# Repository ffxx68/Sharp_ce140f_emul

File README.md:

# Sharp_ce140f_emul
A hardware module emulating the Sharp CE-140F disk drive, using an SD-Card and an STM32 Nucleo microcontroller

At the time (I'm talking about mid '80s early '90s), what I thought my Sharp-PC was missing the most was a convenient way to store and load programs. Entering a BASIC listing by hand has always been one of the most frustrating tasks, in the early days of home computing. Magnetic cassettes using a standard record player used to be the most common (and affordable!) storage medium, back then. Indeed, today a software-emulated cassette interface has been developed too - [PocketTools](http://pocket.free.fr/html/soft/pocket-tools_e.html), but using disks is something definitely different!

The Sharp CE-140F Disk Driver was a rare and expensive extension for the Sharp Pocket PCs, compatible with several models:

PC-1280, PC-1280(Jap), PC-1285, PC-1403, PC-1403H, PC-1425, PC-1425(Jap), PC-1460, PC-1460(Jap), PC-1470U, PC-1475, PC-1475(Jap), EL-5500III, PC-E500, PC-E500(Jap), PC-E500S, PC-E550, PC-E650, PC-U6000. As well as the PC-1360, PC-1360K, PC-1365 and PC-1365K after 1986 (see also: [pocket.free.fr](http://pocket.free.fr/html/sharp/ce-140f_e.html?fbclid=IwAR3U31Bk95W-eKc_V7EStOoxpfgk6qsZ3UOhHXM6cb7czv4wsmH_SPU4H-8)).

The interface presented here is an emulated hardware alternative to the real CE-140F, to get a fully functional disk file management on Sharp PCs, using an SD-card as a storage medium, so that one can manage files from a Sharp PC using a modern PC.

## The PCB board

After optimizing the project with this early prototype, based upon a Nucleo L053R8 controller board (that was one I had at hand, at the time):

an Indiegogo campaign ([Sharp_ce140f_emul on Indiegogo](https://www.indiegogo.com/projects/sharp-ce-140f-disk-drive-emulator/x/32084495#/)) has succesfully crowd-funded the manufacturing of the PCB board version. This PCB holds the Nucleo (here a more powerful L432KC), the SD card, and the interface circuitry:

Here's a demonstration video, using the LOAD and SAVE commands for example, performed with the PCB version of the emulator:
 
[LOAD or SAVE demo](https://www.youtube.com/watch?v=3_DliJE_47g&t=2s)

The complete KiCAD project is public ([KiCad v1 project](https://github.com/ffxx68/Sharp_ce140f_emul/tree/main/KiCad_v1)), while at the following link there's the PCB manufacturer's project, ready for production, in case you wish to order some directly:

[Sharp_ce140f_emul by AISLER](https://aisler.net/p/DIQRWUOC)
[Sharp_ce140f_emul by PCBWay](https://www.pcbway.com/project/shareproject/Sharp_CE_140F_Emulator_0e4ce820.html)

## Hardware interface

Interface schematics (find the complete KiCad project in the repo):

Since the Sharp PC uses a CMOS 5v logic, while the Nucleo board is a 3.3v device, some level-shifting is required in between the two. Nucleo inputs are is 5v-tolerant, so the board inputs could easily accept the Sharp outputs without the need any converter, but the board 3.3v output isn't enough to drive the 5v input on the Sharp. The level converter I choose is one of this type: https://www.sparkfun.com/products/12009 (actually, one of its many clones).

Actually, if I had an Arduino ONE at hand when I first started developing this project, being a 5v board, the voltage level conversion wouldn't have been an issue at all. Migrating to Arduino involves a major reworking of the interface software, now, so it is left to any good-willing developer... 

Finding how to interface the Sharp with the Nucleo has been an interesting journey for me, anyway. I initially struggled a lot, before I got the Nucleo board properly receive the Device Code from the PC, which is the very first step of the communication handshake. At first, using the level converter on each data line and sharing the Nucleo pins for both input and output, the board always received a 0xFF, instead of the exepcted 0x41 (which is, an hardcoded "awake" value issued by the Sharp-PC to the CE140-F). After a number of trials and errors, I found out that the converter kept a constant high value on the Nucleo inputs, regardless of the Sharp setting a low. That was because of the normally high impedance of Sharp-PC outputs, I think.

Whatever, I decided to use different pins of the Nucleo board for the return lines (Nucleo-to-Sharp), removing the level converters for the opposite direction (Sharp-to-Nucleo). See schematics. I also soft-configured Nucleo internal pull-down on each input line (45K resistor, as per datasheet) and added a 10K in series, as in the schematics above, to achieve the 5-to-3.3v divide. Output and input stages are time-separated in the communication protocol, so during output, input pins on Nucleo are set to a PullNone (i.e. high impedance) mode. After these changes, I finally reached a stage where the 0x41 device code, as well as the follow-up command sequence, was correctly received by the board and was ready to be processed in software. That became mainly a software issue then, to understand how to decode and send data back. In this respect, I must mention the excellent job the author of the [Pockemul](https://pockemul.com/) all-software emulator, who first reverse-engineered the communication protocol, starting from a real CE140-F device, an who was so kind to share with me the result of his investigations.

About power, the Sharp and the Nucleo do not share the 5v power line, just gnd. This is to prevent the relatively low capacity internal coin cells to be drained by the Nucleo board. At present, the board is powered through its USB plug. I plan (in very long tem), to make the board battery powered, maybe rechargeable.

**Important Note** - With the Nucleo L432KC, by default the PA_5 (A4) and PA_6 (A5) pins can only be used as Input floating (ADC function). SB16 and SB18 solder bridges (0-ohm resistors, actually) must be removed, in order to use these pins as Digital output and have access to other functions (DigitalOut, SPI, PWM, etc...). Refer to the Nucleo user manual, for more details.

## Alternative hardware designs

An important issue has arised, while testing the finished board on different Sharp PC models (which I didn't hit, while using it on my own PC), having to do with the level converter used in my design. The description and a complete story of its analysis can be found at: [Issue #4](https://github.com/ffxx68/Sharp_ce140f_emul/issues/4).

A relatively easy [workaround](https://github.com/ffxx68/Sharp_ce140f_emul/issues/4#issuecomment-1560580153) was later found, using stronger Pull-up resistors, which seems to fix the problem in most of cases. Still, someone has designed and built alternative version of the board. Like, for example the one suggested by Yuuichi Akagawa:

[YuuichiAkagawa's board](https://github.com/ffxx68/Sharp_ce140f_emul/issues/4#issuecomment-1596058545)

Here, he used integrated level converters (SN74LV1T34), in place of the discrete mosfet-based original solution.

Yet an alternative design was also proposed by Pokoyama Danna:

[Pokoyama Danna's board](https://github.com/ffxx68/Sharp_ce140f_emul/tree/main/Board_v1.5_PoyokomaDanna) (e-mail: [PoyokomaDanna](ac_sent@yahoo.co.jp))

where a programmable device (Renesas SLG46826) was used instead. 

Yet, another interesting interface is that by Wayne Venables [Sharp Manager](https://github.com/codaris/SharpManager), where not only the CE-140F, 
but also the CE-126P cassette and printer interface is emulated, on Arduino plus a Windows counterpart program.

## Emulator software description

The commands implemented are those from the [CE140F Operation Manual](CE140F_OPERATION_MANUAL_EN_DE_FR-compressed.pdf),

| Command                                | Description                                                                                  |
|----------------------------------------|----------------------------------------------------------------------------------------------|
| `LOAD`                                 | ✅ Load a BASIC program to PC memory                                                          |
| `SAVE`                                 | ✅ Save a BASIC program in tokenized, binary format                                           |
| `SAVE ,A`                              | ✅ Save a BASIC program in plain ASCII format                                                 |
| `FILES`                                | ✅ List files, including wildcards (e.g. `FILES"X:C*.BAS"`), and navigation using ↑ ↓ SHIFT+↓ |
| `KILL`                                 | ✅ Delete a file                                                                              |
| `OPEN` / `CLOSE` / `PRINT#` / `INPUT#` | ✅ BASIC statements to handle data files                                                      |
| `DSKF`                                 | ✅ `DSKF 1` returns free Mbytes; `DSKF 2` returns a test dummy value of 65535                 |
| `CHAIN` / `MERGE`                      | ✅ Load and execute a program, with / without deleting the program in PC memory               |
| `EOF`                                  | ✅ BASIC statement to check for end-of-file                                                   |
| `NAME`                                 | ✅ Rename a file                                                                              |
| `SET`                                  | ✅ Set a password to a file                                                                   |
| `COPY`                                 | ✅ Copy a file to a different name (drive letters X:, Y: ignored)                             |
| `LFILES`                               | ✅ List files and attributes to serial printer                                                |
| `LOC` / `LOF`                          | ✅ BASIC statements to get the current position and length of a file                          |
| `INIT`                                 | ❌ Intentionally not implemented (disk formatting)                                            |

The emulator tries to reply as closely as possible (given the knowledge we have at present of the protocol) to the commands issues by the Sharp-PC, 
like an actual CE-140F would. Unfortunately, the official [CE-140F Service Manual](CE140F_Service_manual.pdf) doesn't go beyond the low-level hardware description, 
so some commands may still show some unexpected behaviour. 
Several tests, by different users too, have validated the most common use cases, though.

With respect to the communication protocol, I've tried to summarize here what we know so far:

[Protocol](https://github.com/ffxx68/Sharp_ce140f_emul/blob/main/protocol.md)

## Software installation

Pre-built binaries can be found in

[Releases](https://github.com/ffxx68/Sharp_ce140f_emul/releases)

at various stages in the software evolution, with version numbering suggesting the more recent one.

To install a binary, download the .bin file on your PC and drag the file to the device shown as a virtual disk drive, when plugged in to a PC USB port.
This applies to Windows OS. 

Under Linux, the ST-Link mounts the board as a USB mass storage, e.g. `/Volumes/NODE_L432KC`, `/Volumes/NOD_L432KC`, `/Volumes/NUCLEO*`.

## Software build

The [STM32CubeIDE](https://www.st.com/en/development-tools/stm32cubeide.html) framework 
can be used to build and flash the code found in the `main` branch here, using the included IDE tools. 

Alternatively, a `[Makefile](Makefile)` is provided too, to build and flash from a command line, 
assuming `make` and the Arm GNU Toolchain are available (`arm-none-eabi`, included with the STM32CubeIDE installation).

*NOTE* - The original version of the project (now found in the `legacyMbed` branch) was developed using the Keil Studio Cloud online tools,
which has now reached its [end of life, since July 2026](https://forums.mbed.com/t/important-update-on-mbed-end-of-life/23644).

## Further Evolutions

As noted, version v1 of the board needs to be powered through the board USB plug. 
Making the emulator entirely portable, battery powered, is the most sensible next step that gets to my mind. 
To this aim, I have started a second revision of the board design, aimed mainly at:

- USB-rechargable battery power
- an enclosure-ready PCB form factor
- fixing Issue#4 (see above)

A DRAFT version of this v2 PCB is here: 

https://github.com/ffxx68/Sharp_ce140f_emul/tree/main/KiCad_v2

but it's very far from the making, yet. 
Firmware would need to be revised too.

## Acknowledgements
Many have contributed to make this project what it is.
Among them:

- [Pockemul](https://pockemul.com/) emulator's author, who first reverse engineered the CE-140F protocol
- [Walter](http://www.cavefischer.at/spc/index.htm), who helped me on the hardware interface front
- [POCKET GAMES](https://github.com/phoen1s/SHARP_G-850V_PC-E650/tree/main/DRIVER%20CE-104F%20), 
for the tremendous work he's done to complete the command set, fixing bugs and optimizing the driver overall
- The contributors to the PCB crowdfunding campaign, on Indiegogo.
- The entire community of Sharp-PC enthusiasts.

Thank you all.

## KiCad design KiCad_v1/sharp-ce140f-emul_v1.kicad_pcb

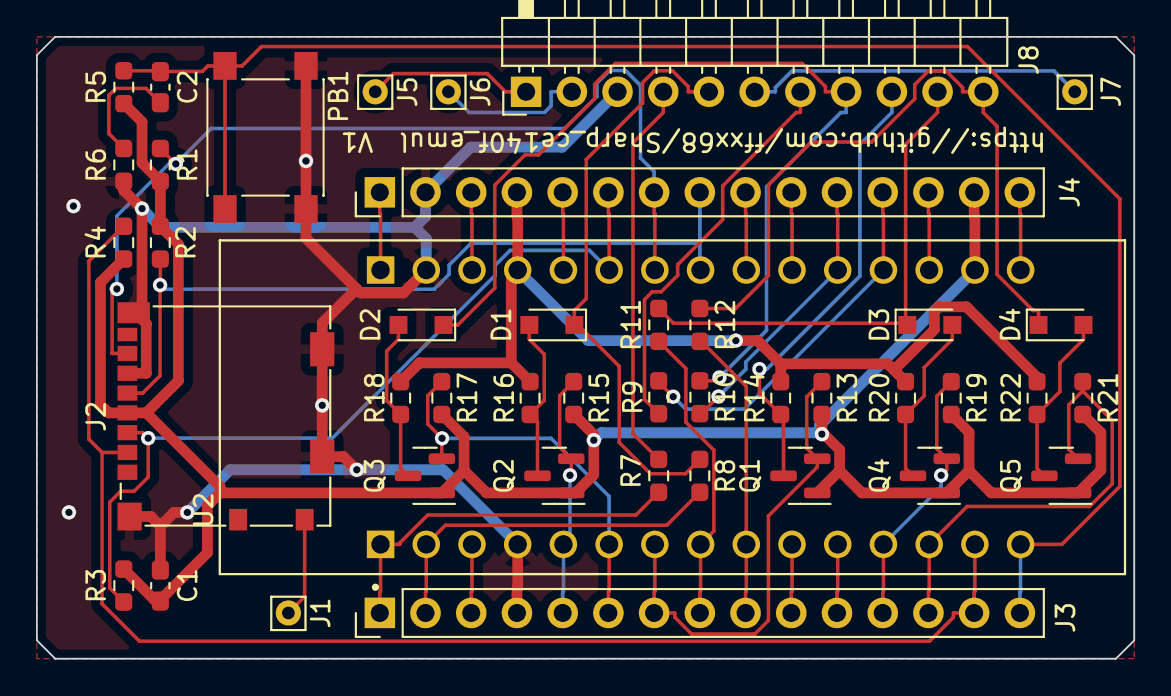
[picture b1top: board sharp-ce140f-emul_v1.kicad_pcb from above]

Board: 2 copper layers, 61.0 x 34.5 mm, 43 parts (0 on the bottom side), 45 nets.

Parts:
C1, C2: 100n; C_0603_1608Metric_Pad1.08x0.95mm_HandSolder
D1, D2, D3, D4: 1N4148; D_SOD-323_HandSoldering
J1, J5, J6, J7: Conn_01x01; Pin_D0.7mm_L6.5mm_W1.8mm_FlatFork
J2: Micro_SD_Card_Det; microSD_HC_Molex_104031-0811
J3, J4: Conn_01x15; PinHeader_1x15_P2.54mm_Vertical
J8: Sharp PC 11-pin; PinHeader_1x11_P2.54mm_Horizontal
PB1: User_button; SW_Push_1P1T_NO_6x6mm_H9.5mm
Q1, Q2, Q3, Q4, Q5: BSS138; SOT-23
R1, R2, R3, R4, R5: 47k; R_0603_1608Metric_Pad0.98x0.95mm_HandSolder
R6: 100; R_0603_1608Metric_Pad0.98x0.95mm_HandSolder
R7, R8, R9, R10, R11, R12, R13, R15, R17, R19, R21: 10k; R_0603_1608Metric_Pad0.98x0.95mm_HandSolder
R14, R16, R18, R20, R22: 5k; R_0603_1608Metric_Pad0.98x0.95mm_HandSolder
U2: NUCLEO-L432KC; MODULE_NUCLEO-L432KC

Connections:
+3V3: C1.1, J2.4 (VDD), J4.14, Q1.1 (G), Q2.1 (G), Q3.1 (G), Q4.1 (G), Q5.1 (G), R1.1, R2.1, R3.1, R4.1, R5.2, R13.2, R15.2, R17.2, R19.2, R21.2, U2.CN4_14 (+3V3)
+5V: J4.4, R14.2, R16.2, R18.2, R20.2, R22.2, U2.CN4_4 (+5V)
/Level Conv2/conv_HV: D1.2 (A), Q2.3 (D), R16.1
/Level Conv3/conv_HV: D2.2 (A), Q3.3 (D), R18.1
/Level Conv4/conv_HV: D3.2 (A), Q4.3 (D), R20.1
/Level Conv5/conv_HV: D4.2 (A), Q5.3 (D), R22.1
/conn_ack: J8.9 (ACK), Q1.3 (D), R14.1
/conn_busy: J8.4 (BUSY), R7.1
/conn_din: D2.1 (K), J8.8 (DIN), R10.1
/conn_dout: D1.1 (K), J8.5 (DOUT), R8.1
/conn_mtout2: J5.1, J8.1 (MT_OUT2)
/conn_sel1: D4.1 (K), J8.11 (SEL1), R12.1
/conn_sel2: D3.1 (K), J8.10 (SEL2), R11.1
/conn_vgg: J6.1, J8.2 (VGG)
/conn_xin: J7.1, J8.6 (X_IN)
/conn_xout: J8.7 (X_OUT), R9.1
/rc_btn: C2.2, R6.2
/sd_cd: J1.1, J2.10 (DET_A)
CN3_1: J3.1, R7.2, U2.CN3_1 (PA9)
CN3_2: J3.2, R8.2, U2.CN3_2 (PA10)
CN3_3: J3.3, U2.CN3_3 (NRST_CN3)
CN3_5: J3.5, Q2.2 (S), R15.1, U2.CN3_5 (PA12)
CN3_6: J3.6, Q3.2 (S), R17.1, U2.CN3_6 (PB0)
CN3_7: J3.7, Q1.2 (S), R13.1, U2.CN3_7 (PB7)
CN3_8: J3.8, R11.2, U2.CN3_8 (PB6)
CN3_9: J3.9, R12.2, U2.CN3_9 (PB1)
CN3_10: J3.10, U2.CN3_10 (D7)
CN3_11: J3.11, U2.CN3_11 (D8)
CN3_12: J3.12, Q4.2 (S), R19.1, U2.CN3_12 (PA8)
CN3_13: J3.13, Q5.2 (S), R21.1, U2.CN3_13 (PA11)
CN3_14: J2.2 (DAT3/CD), J3.14, R4.2, U2.CN3_14 (PB5)
CN3_15: C2.1, J3.15, PB1.1, R5.1, U2.CN3_15 (PB4)
CN4_1: J4.1, U2.CN4_1 (VIN)
CN4_3: J4.3, U2.CN4_3 (NRST_CN4)
CN4_5: J4.5, U2.CN4_5 (PA2)
CN4_6: J2.3 (CMD), J4.6, R3.2, U2.CN4_6 (PA7)
CN4_7: J2.7 (DAT0), J4.7, R1.2, U2.CN4_7 (PA6)
CN4_8: J2.5 (CLK), J4.8, R2.2, U2.CN4_8 (PA5)
CN4_9: J4.9, U2.CN4_9 (PA4)
CN4_10: J4.10, U2.CN4_10 (PA3)
CN4_11: J4.11, R10.2, U2.CN4_11 (PA1)
CN4_12: J4.12, R9.2, U2.CN4_12 (PA0)
CN4_13: J4.13, U2.CN4_13 (AREF)
CN4_15: J4.15, U2.CN4_15 (PB3)
GND: C1.2, J2.6 (VSS), J2.11 (SHIELD), J3.4, J4.2, J8.3 (GND), PB1.2, R6.1, U2.CN3_4 (GND_CN3), U2.CN4_2 (GND_CN4)

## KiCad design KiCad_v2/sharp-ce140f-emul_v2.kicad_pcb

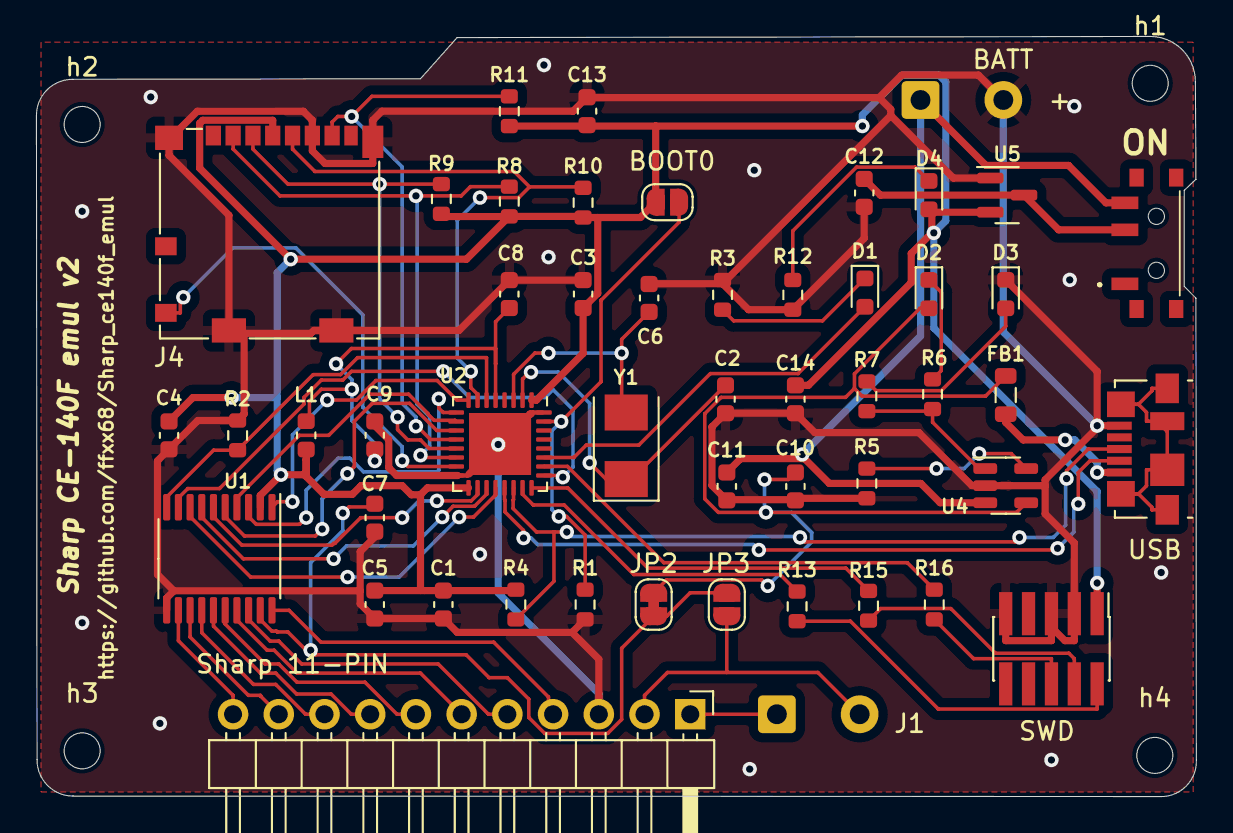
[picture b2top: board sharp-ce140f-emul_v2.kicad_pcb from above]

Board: 2 copper layers, 64.4 x 42.2 mm, 54 parts (0 on the bottom side), 50 nets.

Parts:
BATT: Battery; SolderWire-0.5sqmm_1x02_P4.6mm_D0.9mm_OD2.1mm
BOOT0: BOOT0; SolderJumper-2_P1.3mm_Open_RoundedPad1.0x1.5mm
C1, C10, C11: 4u7; C_0603_1608Metric
C2, C6: 10p; C_0603_1608Metric
C3, C4, C5, C7, C9, C13: 100n; C_0603_1608Metric
C8, C12, C14: 1u; C_0603_1608Metric
D1: green; LED_0603_1608Metric
D2, D3: Blue; LED_0603_1608Metric
D4: red; LED_0603_1608Metric
FB1: 100R; L_0805_2012Metric
J1: ext pins; SolderWire-0.5sqmm_1x02_P4.6mm_D0.9mm_OD2.1mm
J4: Micro_SD_Card_Det; microSD_HC_Molex_104031-0811
JP2: 5V_VPP; SolderJumper-2_P1.3mm_Bridged_RoundedPad1.0x1.5mm
JP3: 5V_VGG; SolderJumper-2_P1.3mm_Open_RoundedPad1.0x1.5mm
L1: 27n; L_0603_1608Metric
ON: PCM12SMTR
R1, R5: 10k; R_0603_1608Metric
R2, R3, R4, R12: 1k5; R_0603_1608Metric
R6, R7: 2K2; R_0603_1608Metric
R8, R9, R10, R11: 47k; R_0603_1608Metric
R13, R15, R16: 22; R_0603_1608Metric
SWD: SWD; PinHeader_2x05_P1.27mm_Vertical_SMD
Sharp 11-PIN: Sharp PC 11-pin; PinHeader_1x11_P2.54mm_Horizontal
U1: TXS0108EPW; TSSOP-20_4.4x6.5mm_P0.65mm
U2: STM32L432KCUx; QFN-32-1EP_5x5mm_P0.5mm_EP3.45x3.45mm
U4: MCP73831; SOT-23-5
U5: XC6206P332MR; SOT-23
USB: USB_B_Micro; USB_Micro-B_Molex_47346-0001
Y1: 32.768KHz; Crystal_SMD_5032-2Pin_5.0x3.2mm
h1, h2, h3, h4: MountingHole_2mm

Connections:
+3.3VA: C8.1, C9.1, L1.2, U2.5 (VDDA)
+3V3: BOOT0.2 (B), C1.1, C3.1, C4.1, C5.1, C13.1, C14.1, D4.2 (A), J4.4 (VDD), L1.1, R4.1, R8.1, R9.1, R10.1, R11.1, SWD.1, U1.2 (VCCA), U2.1 (VDD), U2.17 (VDD), U5.2 (VO)
+5V: FB1.2, USB.1 (VBUS)
/BOOT0: BOOT0.1 (A), R1.1, U2.31 (PH3)
/HSE_IN: C2.1, U2.2 (PC14), Y1.1
/HSE_OUT: C6.1, U2.3 (PC15), Y1.2
/V_BAT: BATT.1, C11.1, ON.3 (NO), U4.3 (VBAT)
/ack: Sharp 11-PIN.9 (ACK), U1.14 (B6)
/busy: Sharp 11-PIN.4 (BUSY), U1.20 (B1)
/din: Sharp 11-PIN.8 (DIN), U1.15 (B5)
/dout: Sharp 11-PIN.5 (DOUT), U1.18 (B2)
/mt_out2: J1.1, Sharp 11-PIN.1 (MT_OUT2)
/sel1: Sharp 11-PIN.11 (SEL1), U1.12 (B8)
/sel2: Sharp 11-PIN.10 (SEL2), U1.13 (B7)
/usr_led: D1.2 (A), U2.27 (PB4)
/vccb: C7.1, JP2.1 (A), JP3.1 (A), U1.19 (VCCB)
/vgg: J1.2, JP3.2 (B), Sharp 11-PIN.2 (VGG)
/x_in: Sharp 11-PIN.6 (X_IN), U1.17 (B3)
/x_out: Sharp 11-PIN.7 (X_OUT), U1.16 (B4)
GND: BATT.2, C1.2, C2.2, C3.2, C4.2, C5.2, C6.2, C7.2, C8.2, C9.2, C10.2, C11.2, C12.2, C13.2, C14.2, D3.1 (K), J4.6 (VSS), J4.11 (SHIELD), R1.2, R2.1, R3.2, R5.2, R12.2, SWD.3, SWD.5, SWD.9, Sharp 11-PIN.3 (GND), U1.11 (GND), U2.16 (VSS), U2.32 (VSS), U2.33 (VSS), U4.2 (VSS), U5.1 (GND), USB.5 (GND)
unnamed: D1.1 (K), R3.1
unnamed: D2.1 (K), R6.1
unnamed: D3.2 (A), R7.1
unnamed: D4.1 (K), R12.1
unnamed: R13.2, SWD.2
unnamed: R15.2, SWD.4
unnamed: R16.2, SWD.6
unnamed: R5.1, U4.5 (PROG)
unnamed: R6.2, R7.2, U4.1 (STAT)
PA0: R2.2, U1.10 (OE), U2.6 (PA0)
PA2: U1.1 (A1), U2.8 (PA2)
PA3: U1.3 (A2), U2.9 (PA3)
PA4: U1.4 (A3), U2.10 (PA4)
PA5: U1.5 (A4), U2.11 (PA5)
PA8: U1.6 (A5), U2.18 (PA8)
PA9: U1.7 (A6), U2.19 (PA9)
PA10: U1.8 (A7), U2.20 (PA10)
PA15: U1.9 (A8), U2.25 (PA15)
SD_CD: J4.10 (DET_A), U2.15 (PB1)
SD_CS: J4.2 (DAT3/CD), R8.2, U2.14 (PB0)
SPI1_MISO: J4.7 (DAT0), R11.2, U2.12 (PA6)
SPI1_MOSI: J4.3 (CMD), R9.2, U2.13 (PA7)
SPI1_SCK: J4.5 (CLK), R10.2, U2.7 (PA1)
SWCLK: R15.1, U2.24 (PA14)
SWDIO: R13.1, U2.23 (PA13)
SWO: R16.1, U2.26 (PB3)
USB_D+: R4.2, U2.22 (PA12), USB.3 (D+)
USB_D-: U2.21 (PA11), USB.2 (D-)
VCC: C12.1, ON.2 (COM), U5.3 (VI)
VPP: C10.1, D2.2 (A), FB1.1, JP2.2 (B), U4.4 (VDD)

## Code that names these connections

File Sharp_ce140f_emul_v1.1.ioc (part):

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Mcu.Name=STM32L432K(B-C)Ux
Mcu.Package=UFQFPN32
Mcu.UserName=STM32L432KCUx
PA0.GPIOParameters=GPIO_Label
PA0.GPIO_Label=in_X_OUT
PA0.Signal=GPXTI0
PA1.GPIOParameters=GPIO_Label
PA1.GPIO_Label=in_D_IN
PA1.Signal=GPIO_Input
PA10.GPIOParameters=GPIO_Label
PA10.GPIO_Label=in_D_OUT
PA10.Signal=GPIO_Input
PA11.GPIOParameters=GPIO_Label
PA11.GPIO_Label=out_SEL_1
PA11.Signal=GPIO_Output
PA12.GPIOParameters=GPIO_Label
PA12.GPIO_Label=out_D_OUT
PA12.Signal=GPIO_Output
PA13\ (JTMS-SWDIO).GPIOParameters=GPIO_Label
PA13\ (JTMS-SWDIO).GPIO_Label=SWDIO
PA13\ (JTMS-SWDIO).Mode=Serial_Wire
PA13\ (JTMS-SWDIO).Signal=SYS_JTMS-SWDIO
PA14\ (JTCK-SWCLK).GPIOParameters=GPIO_Label
PA14\ (JTCK-SWCLK).GPIO_Label=SWCLK
PA14\ (JTCK-SWCLK).Mode=Serial_Wire
PA14\ (JTCK-SWCLK).Signal=SYS_JTCK-SWCLK
PA15\ (JTDI).GPIOParameters=GPIO_Label
PA15\ (JTDI).GPIO_Label=VCP_RX
PA15\ (JTDI).Mode=Asynchronous
PA15\ (JTDI).Signal=USART2_RX
PA2.GPIOParameters=GPIO_Label
PA2.GPIO_Label=VCP_TX
PA2.Mode=Asynchronous
PA2.Signal=USART2_TX
PA8.GPIOParameters=GPIO_Label
PA8.GPIO_Label=out_SEL_2
PA8.Signal=GPIO_Output
PA9.GPIOParameters=GPIO_Label
PA9.GPIO_Label=in_BUSY
PA9.Signal=GPXTI9
PB0.GPIOParameters=GPIO_Label
PB0.GPIO_Label=out_D_IN
PB0.Signal=GPIO_Output
PB1.GPIOParameters=GPIO_Label
PB1.GPIO_Label=in_SEL_1
PB1.Signal=GPIO_Input
PB3\ (JTDO-TRACESWO).GPIOParameters=GPIO_Label
PB3\ (JTDO-TRACESWO).GPIO_Label=infoLed
PB3\ (JTDO-TRACESWO).Signal=GPIO_Output
PB4\ (NJTRST).GPIOParameters=GPIO_Label
PB4\ (NJTRST).GPIO_Label=user_BTN
PB4\ (NJTRST).Signal=GPXTI4
PB6.GPIOParameters=GPIO_Label
PB6.GPIO_Label=in_SEL_2
PB6.Signal=GPIO_Input
PB7.GPIOParameters=GPIO_Label
PB7.GPIO_Label=out_ACK
PB7.Signal=GPIO_Output
PC14-OSC32_IN\ (PC14).Signal=RCC_OSC32_IN
PC15-OSC32_OUT\ (PC15).Signal=RCC_OSC32_OUT
RCC.HSE_VALUE=8000000
RCC.SYSCLKFreq_VALUE=32000000
RCC.SYSCLKSource=RCC_SYSCLKSOURCE_PLLCLK
board=NUCLEO-L432KC
boardIOC=true

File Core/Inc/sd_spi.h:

/*
 * sd_spi.h - MMC/SDC (in SPI mode) low level driver for the CE-140F emulator
 *
 * PCB v1 wiring (Nucleo-L432KC):
 *    SCK  = PA5  (SPI1_SCK,  AF5)   NOTE: solder bridge SB16 must be open
 *    MISO = PA6  (SPI1_MISO, AF5)   NOTE: solder bridge SB18 must be open
 *    MOSI = PA7  (SPI1_MOSI, AF5)
 *    CS   = PB5  (plain GPIO output)
 *
 * This is the layer the CubeMX-generated FATFS/Target/user_diskio.c skeleton
 * was missing: without it every f_mount()/f_open() call fails and the emulator
 * can only answer commands that do not touch the card.
 */
#ifndef SD_SPI_H
#define SD_SPI_H

#include "main.h"
#include "ffconf.h"
#include "diskio.h"

#ifdef __cplusplus
extern "C" {
#endif

/* SPI clock = PCLK2 / prescaler, written straight into CR1_BR.
   PCLK2 is 32 MHz with the current clock tree. */
#define SD_SPI_PRESCALER_SLOW   (6u << SPI_CR1_BR_Pos)  /* /128 -> 250 kHz, card init */
#define SD_SPI_PRESCALER_FAST   (2u << SPI_CR1_BR_Pos)  /* /8   -> 4 MHz, normal use  */

#define SD_CS_Pin               GPIO_PIN_5
#define SD_CS_GPIO_Port         GPIOB

/* Configures SPI1 and the CS pin. Call once, before MX_FATFS_Init(). */
void SD_SPI_Init(void);

/* diskio back-end */
DSTATUS SD_disk_initialize(void);
DSTATUS SD_disk_status(void);
DRESULT SD_disk_read(BYTE *buff, DWORD sector, UINT count);
DRESULT SD_disk_write(const BYTE *buff, DWORD sector, UINT count);
DRESULT SD_disk_ioctl(BYTE cmd, void *buff);

#ifdef __cplusplus
}
#endif

#endif /* SD_SPI_H */

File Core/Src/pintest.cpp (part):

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// prints them grouped.
static const PinDef pinTable[] = {
    // --- outputs (emulator -> Sharp PC, via the level converter) ---
    { "ack",    out_ACK_GPIO_Port,   out_ACK_Pin,   true  },
    { "dout",   out_D_OUT_GPIO_Port, out_D_OUT_Pin, true  },
    { "din",    out_D_IN_GPIO_Port,  out_D_IN_Pin,  true  },
    { "sel1",   out_SEL_1_GPIO_Port, out_SEL_1_Pin, true  },
    { "sel2",   out_SEL_2_GPIO_Port, out_SEL_2_Pin, true  },
    { "led",    infoLed_GPIO_Port,   infoLed_Pin,   true  },
    // --- inputs (Sharp PC -> emulator) ---
    { "ibusy",  in_BUSY_GPIO_Port,   in_BUSY_Pin,   false },
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#define PIN_COUNT ((int)(sizeof(pinTable) / sizeof(pinTable[0])))

// The four data lines, LSB first, as used by the protocol nibble encoding.
static const int nibbleOutIdx[4] = { 3, 4, 1, 2 }; // sel1, sel2, dout, din
static const int nibbleInIdx[4]  = { 10, 11, 8, 9 }; // isel1, isel2, idout, idin

static bool testActive = false;
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    tp_print("  low              drive every output low\r\n");
    tp_print("  help             this text\r\n");
    tp_print("  exit             leave test mode, resume protocol\r\n");
    tp_print("pins: ack dout din sel1 sel2 led | ibusy ixout idout idin isel1 isel2\r\n");
}

// ---------------------------------------------------------------------------
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
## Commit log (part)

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2022-04-22 First version, not tested yet, of an emulator for the Sharp CE-140F Diskette Driver
2022-04-25 revised connector access methods
2022-04-26 Readme added
2022-04-26 readme update
2022-05-05 New setup to get the device code
2022-05-05 Correct schematics
2022-05-09 New schematics and results
2022-05-09 Corrected readme
2022-05-20 changed approach - using interrupts
2022-05-20 changed approach, using interrupts
2022-05-24 Acknowledgements
2022-05-25 minor revision
2022-05-25 Updating schematics and status update
2022-06-08 Fixed input data handshake
2022-06-14 Completed command receive sequence
2022-06-14 command code debug example
2022-06-15 Draft versione processing the DSKF command
2022-06-15 Draft version processing the DSKF command
2022-06-15 New interface with return lines
2022-07-14 edited readme
2022-07-19 Added SD card handling and basic FILES command processing (under testing yet)
2022-07-19 minor change
2022-07-21 updated schematics, to include the SD card
2022-07-21 Edited text
2022-07-21 Fixed schematics
2022-07-21 Picture added
2022-07-25 Added command processing
2022-07-25 Readme
2022-07-25 readme editing
2022-07-27 build notes
2022-07-27 new build notes
2022-07-27 editing
2022-07-29 updated schematics
2022-07-30 fixed output mode pins
2022-07-30 demo update
2022-07-30 fixed description
2022-07-30 dskf command clarification
2022-07-30 minor editing
2022-09-17 FILES command processing added
2022-09-17 FILES command video
2022-09-17 edit
2022-09-17 more editing
2022-09-22 schematics fix and text editing
2022-09-22 further schematics retouch
2022-09-23 LOAD command changes (though not working yet)
2022-09-27 SAVE command introduced (not working yet)
2022-09-30 LOAD (non-ASCII) command complete
2022-10-21 new prototype version
2022-11-16 Initial upgrade to the L432KC Nucleo board
2022-11-16 Show L432KC prototype
2022-11-16 reamde update
2022-11-20 fixed LOAD 0x0F command (non-ascii files, e.g. BASIC)
2022-11-22 Further minor fixes
2022-11-22 editing readme
2022-11-28 Further fixes (SAVE is still not working...)
2022-11-28 emulator software description
2022-11-29 editing of software description
2022-11-29 CE-140F Operation and Service manuals
2022-12-11 SAVE (binary file, 0xFF command) fixed
2022-12-22 Reworking of the SAVE command (but ASCII mode 0x16 not working yet)
2023-01-05 communication protocol description
2023-01-05 images and editing added
2023-01-05 protocol document reference
2023-01-05 sequential vs. asynchronous approaches
2023-01-05 links
2023-01-12 SAVE and LOAD complete
2023-01-12 New video linked
2023-01-18 KiCad project added
2023-01-18 schematics image
2023-01-23 PCB review
2023-01-23 new PCB version
2023-01-31 Indiegogo campaign
2023-02-01 some footprint review and BOM exported (csv)
2023-02-07 Final review before PCB manufacturing
2023-03-03 editing text
2023-03-03 Assembled PCB picture
2023-03-04 PC-E500 series support
    PC-E500 series support
2023-03-04 Fixed filename handling issues
    Correction of Issues #1
    https://github.com/ffxx68/Sharp_ce140f_emul/issues/1
2023-03-09 PCB version tested on real board
2023-03-22 file OPEN, PRINT#, INPUT# initial implementation
2023-03-23 fixed PRINT# on comma-separated multiple values
2023-04-06 HW Note
2023-04-18 indiegogo campaign update
2023-04-18 Updated demo video link
2023-04-26 AISLER link
2023-04-27 Changed some delays. Added KILL, OPEN, PRINT#, INPUT#
2023-05-15 Changed DSKF return value to 4680
2023-05-25 Level converter simulation, using KiCad + ngspice
2023-05-25 Fixed simulation design
2023-05-29 Updated KiCad project to latest revision
2023-05-29 Added .gitignore (for local-only files)
2023-05-30 Updated KiCad project
2023-06-09 Changed DSKF output
2023-06-19 New version v2 - under development
2023-06-19 Rollback to tag v1.5
2023-06-19 new hardware v2 - DRAFT!
2023-08-02 New board version (DipTrace and GreenPAK files).
2023-08-02 Yamamura's design
2023-08-04 Renaming dir
2023-10-12 DRAFT v2 schematics revisions
2023-11-28 Fix to PRINT# and INPUT# processing
2023-11-28 removing unecessary files
2023-12-13 Some changes to the README
2024-06-05 typos fixed
2024-07-30 MBedOS end of life announced
2024-08-26 PCBWay and editing
2024-09-03 Emulator manual, by Christian Becker
2024-10-16 DSKF upgrade
2024-10-18 Added watchdog on ASCII LOAD
2024-12-02 trying to fix INPUT for number arrays
2025-08-04 Increased file buffer size
2025-09-02 included Wayne's contribution
2025-09-02 readme update and fix
2025-09-05 added console feedback
